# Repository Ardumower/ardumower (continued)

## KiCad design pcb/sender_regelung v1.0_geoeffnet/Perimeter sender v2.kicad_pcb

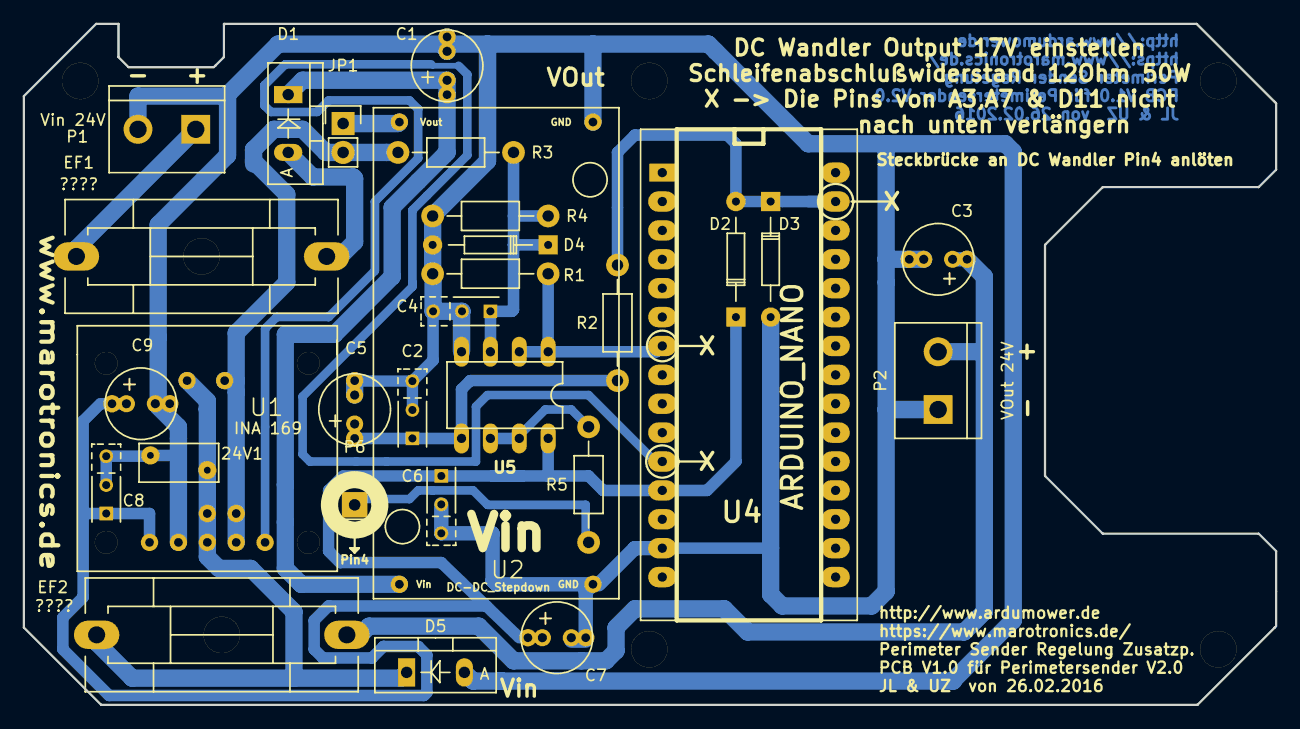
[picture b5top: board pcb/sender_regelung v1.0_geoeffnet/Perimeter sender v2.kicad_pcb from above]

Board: 2 copper layers, 110.1 x 59.9 mm, 35 parts (0 on the bottom side), 16 nets.

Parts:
24V1: VR; RV_Disc_D7_W3.4_P5
B1, B2, B3, B5, B6: Bohrloch_3,2mm
C1, C3: 220uF/63V; Elko_vert_11.2x6.3mm_RM2.5_RM5.0
C2: 220nF; C_Rect_L4_W2.5_P2.5_P5.0
C4: 47pP; C_Rect_L4_W2.5_P2.5_P5.0
C5: 47uF/16V; Elko_vert_11.2x6.3mm_RM2.5_RM5.0
C6, C8: 100nF; C_Rect_L4_W2.5_P2.5_P5.0
C7, C9: 10uF/16V; Elko_vert_11.2x6.3mm_RM2.5_RM5.0
D1, D5: MBR 1045; Diode_TO-220_Vertical
D2, D3: 1N4148; Diode_DO-35_SOD27_Horizontal_RM10
D4: ZPD5,1V; Diode_DO-35_SOD27_Horizontal_RM10
EF1, EF2: ????; Fuseholder_Reichelt_PL112000
JP1: PWR; Pin_Header_Straight_1x02
P1: Vin 24V; Anschlussklemme_2P_RM5,08
P2: VOut 24V; Anschlussklemme_2P_RM5,08
P6: Pin4; Pin_Header_Straight_1x01
R1, R4: 10K/1%; Resistor_Horizontal_RM10mm
R2: 47K; Resistor_Horizontal_RM10mm
R3: 100K/1%; Resistor_Horizontal_RM10mm
R5: 1K; Resistor_Horizontal_RM10mm
U1: INA 169; INA169
U2: DC-DC_Stepdown; DC_DC_DSN2596_mit_Bohrloch
U4: ARDUINO_NANO; arduino_nano
U5: OPA2340PA; 40xx-DIL08

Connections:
+5V: C6.1, C7.1, C8.1, C9.1, D2.1, U1.1, U4.5V, U5.8
A3: R1.1, U4.A3, U5.1, U5.2
A7: U1.3, U4.A7
D11: D2.2, D3.1, R2.2, U4.D11
DC_Wandler_Pin_4: P6.1, R5.1
GND: 24V1.2, C1.2, C2.2, C3.2, C4.2, C5.2, C6.2, C7.2, C8.2, C9.2, D3.2, D4.2, D5.2, P1.2, P2.1, R1.2, R4.2, U1.2, U2.1, U2.4, U4.GND1, U5.4
unnamed: 24V1.1, D5.1, EF2.2, U1.5
unnamed: C1.1, D1.1, U2.3
unnamed: C2.1, C5.1, R2.1, U5.5
unnamed: C3.1, EF2.1, P2.2
unnamed: C4.1, D4.1, R3.2, R4.1, U5.3
unnamed: D1.2, EF1.1
unnamed: EF1.2, P1.1
unnamed: JP1.1, U2.2
unnamed: JP1.2, R3.1, U1.4
unnamed: R5.2, U5.6, U5.7

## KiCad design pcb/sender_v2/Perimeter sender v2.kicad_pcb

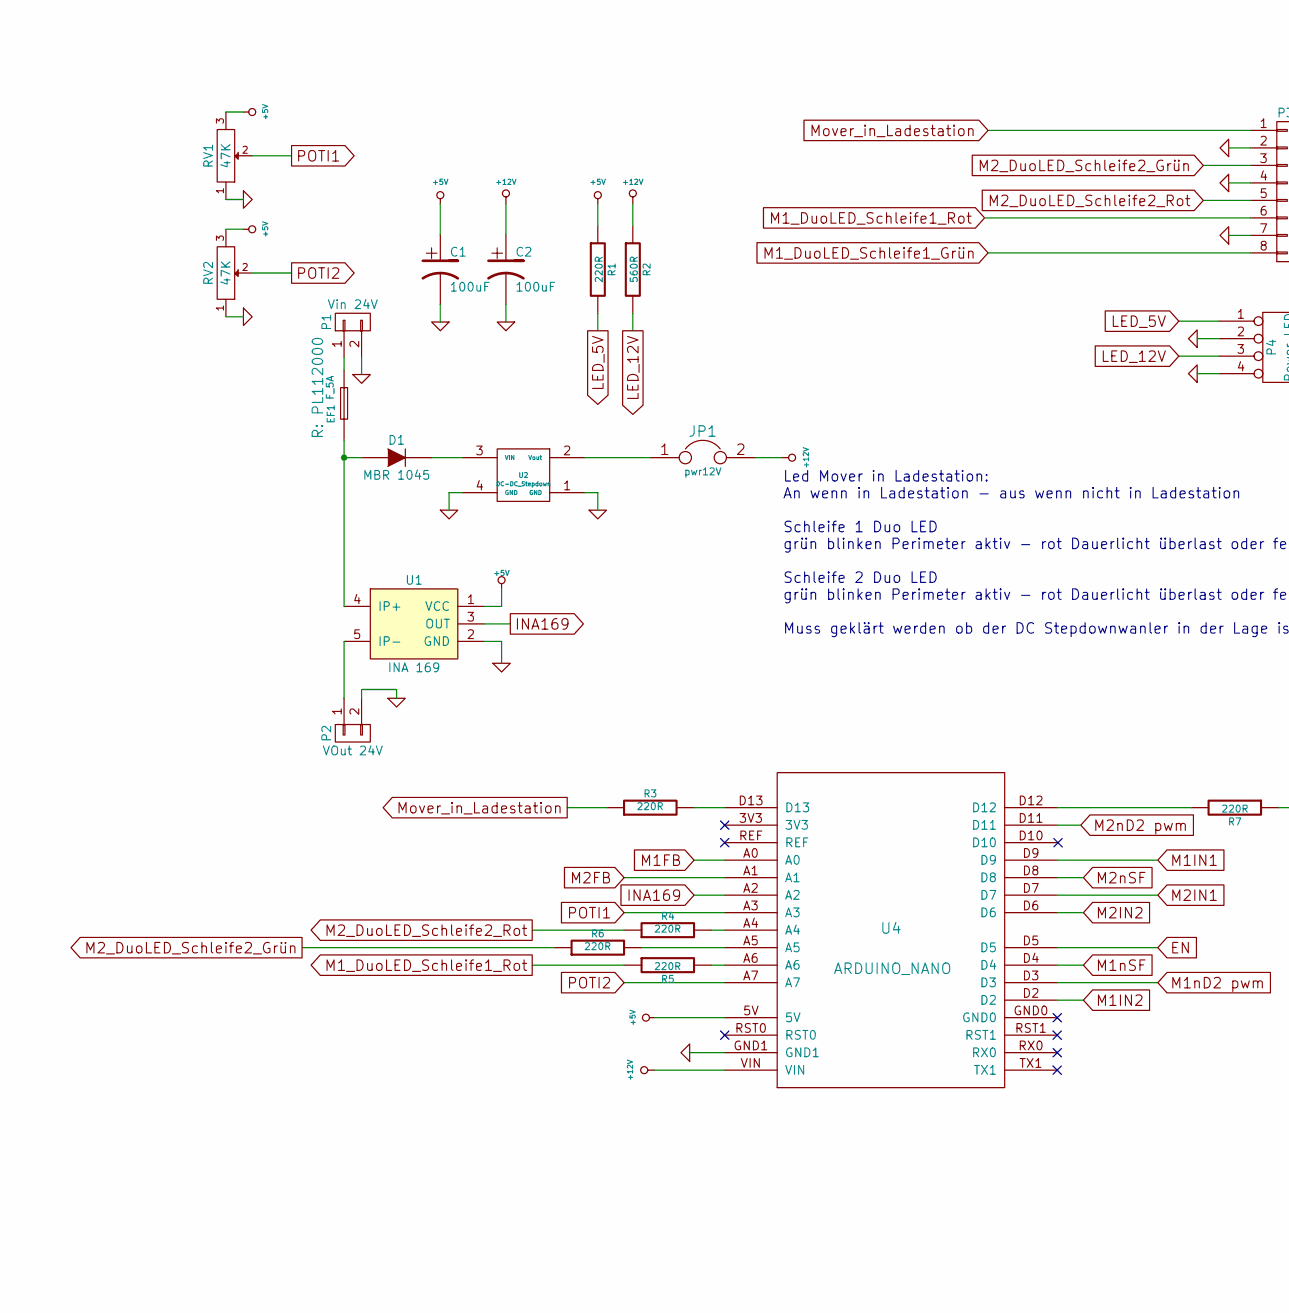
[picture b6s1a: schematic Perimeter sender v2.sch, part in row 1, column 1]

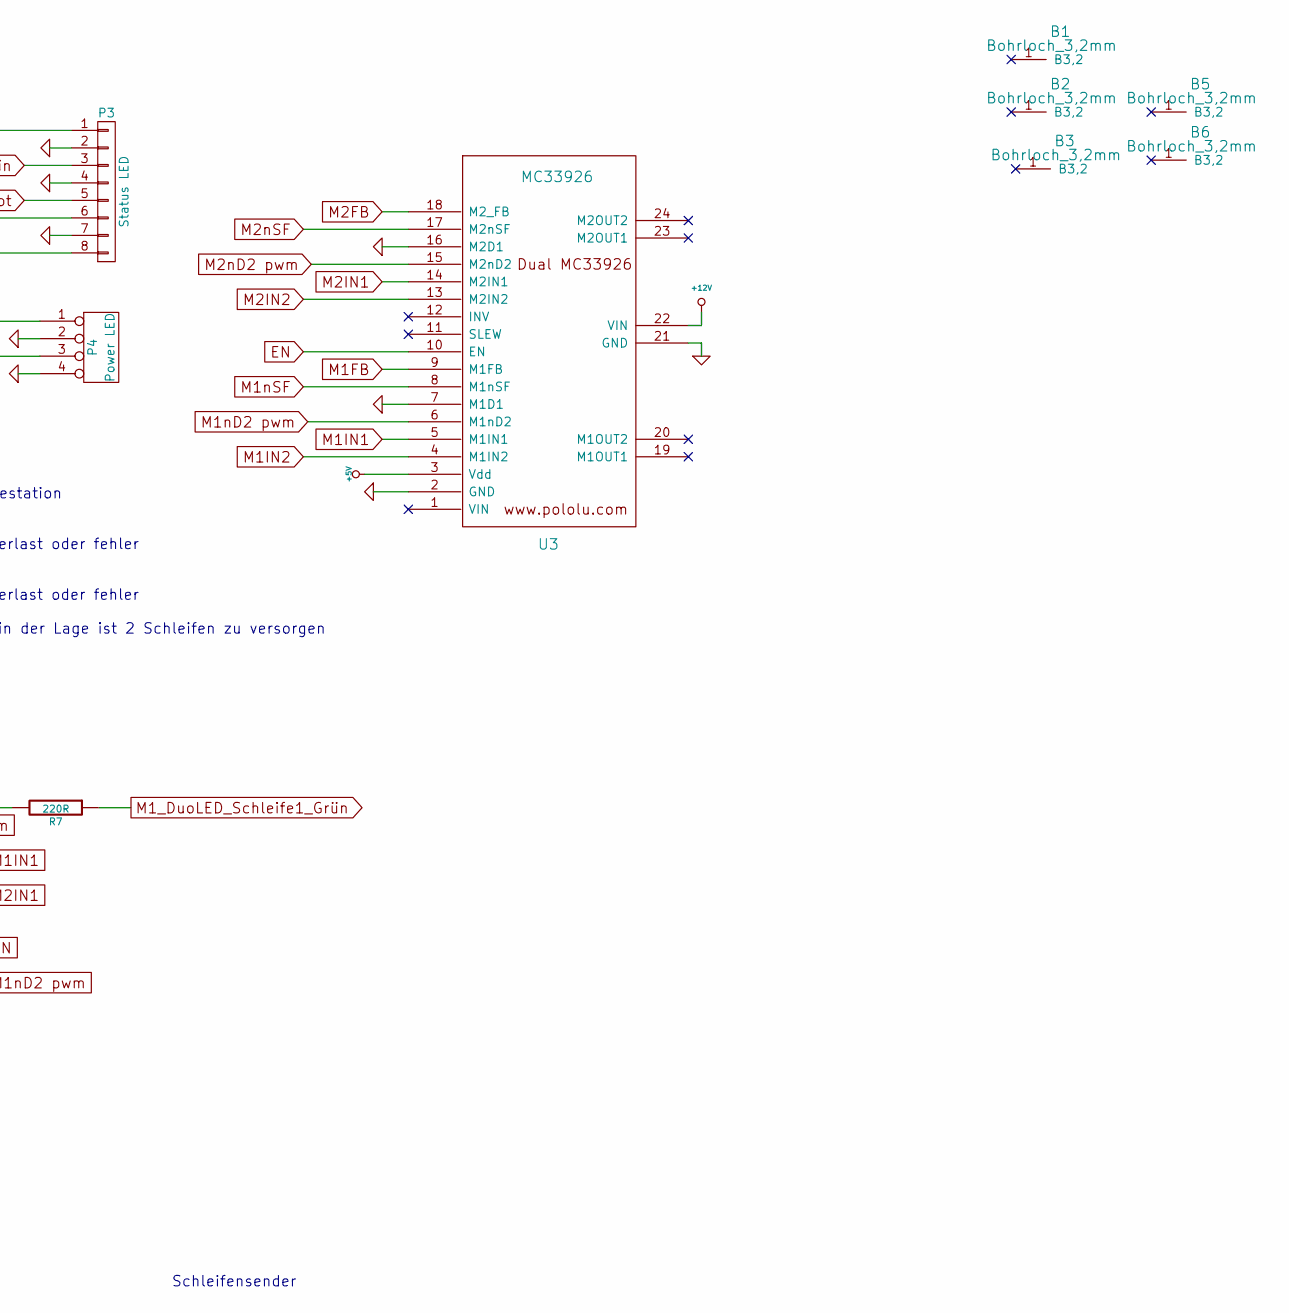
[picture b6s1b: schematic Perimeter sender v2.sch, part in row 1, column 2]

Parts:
B1, B2, B3, B5, B6: Bohrloch_3,2mm
C1, C2: 100uF; Elko_vert_11.2x6.3mm_RM2.5_RM5.0
D1: MBR 1045; MBR1045_Horizontal
EF1: F_5A; Fuseholder_Reichelt_PL112000
JP1: pwr12V; Pin_Header_Straight_1x02
P1: Vin 24V; Anschlussklemme_2P_RM5,08
P2: VOut 24V; Anschlussklemme_2P_RM5,08
P3: Status LED; Pin_Header_Straight_1x08
P4: Power LED; Pin_Header_Straight_1x04
R1, R3, R4, R5, R6, R7: 220R; Resistor_Horizontal_RM10mm
R2: 560R; Resistor_Horizontal_RM10mm
RV1, RV2: 47K; Potentiometer_VishaySpectrol-Econtrim-Type36T_3D-angepasst_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
U1: INA 169; INA169
U2: DC-DC_Stepdown; DC_DC_DSN2596_mit_Bohrloch
U3: MC33926; MC_33926_31polig_mit_Bohrloch_neue_Masse
U4: ARDUINO_NANO; arduino_nano

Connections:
+5V: C1.1, R1.1, RV1.3, RV2.3, U1.1 (VCC), U3.3 (Vdd), U4.5V
+12V: C2.1, JP1.2, R2.1, U3.22 (VIN), U4.VIN
EN: U3.10 (EN), U4.D5
GND: C1.2, C2.2, P1.2, P2.2, P3.2, P3.4, P3.7, P4.2, P4.4, RV1.1, RV2.1, U1.2 (GND), U2.1 (GND), U2.4 (GND), U3.2 (GND), U3.7 (M1D1), U3.16 (M2D1), U3.21 (GND), U4.GND1
INA169: U1.3 (OUT), U4.A2
LED_5V: P4.1, R1.2
LED_12V: P4.3, R2.2
M1FB: U3.9 (M1FB), U4.A0
M1IN1: U3.5 (M1IN1), U4.D9
M1IN2: U3.4 (M1IN2), U4.D2
M1_DuoLED_Schleife1_Grün: P3.8, R7.1
M1_DuoLED_Schleife1_Rot: P3.6, R5.1
M1nD2 pwm: U3.6 (M1nD2), U4.D3
M1nSF: U3.8 (M1nSF), U4.D4
M2FB: U3.18 (M2_FB), U4.A1
M2IN1: U3.14 (M2IN1), U4.D7
M2IN2: U3.13 (M2IN2), U4.D6
M2_DuoLED_Schleife2_Grün: P3.3, R6.1
M2_DuoLED_Schleife2_Rot: P3.5, R4.1
M2nD2 pwm: U3.15 (M2nD2), U4.D11
M2nSF: U3.17 (M2nSF), U4.D8
Mover_in_Ladestation: P3.1, R3.1
unnamed: D1.1 (A), EF1.1, U1.4 (IP+)
unnamed: D1.2 (K), U2.3 (VIN)
unnamed: EF1.2, P1.1
unnamed: JP1.1, U2.2 (Vout)
unnamed: P2.1, U1.5 (IP-)
unnamed: R3.2, U4.D13
unnamed: R4.2, U4.A4
unnamed: R5.2, U4.A6
unnamed: R6.2, U4.A5
unnamed: R7.2, U4.D12
POTI1: RV1.2, U4.A3
POTI2: RV2.2, U4.A7

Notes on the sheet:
Led Mover in Ladestation: An wenn in Ladestation - aus wenn nicht in Ladestation Schleife 1 Duo LED grün blinken Perimeter aktiv - rot Dauerlicht überlast oder fehler Schleife 2 Duo LED grün blinken Perimeter aktiv - rot Dauerlicht überlast oder fehler Muss geklärt werden ob der DC Stepdownwanler i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
Schleifensender

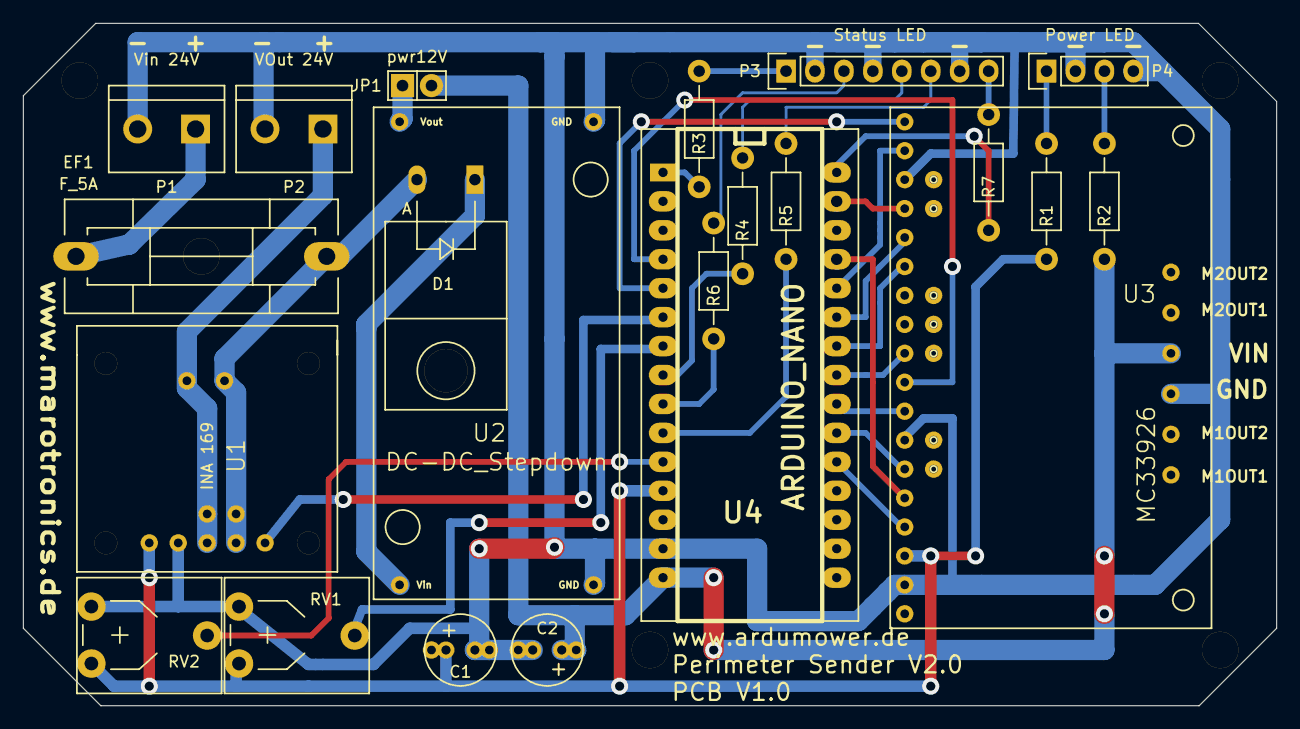
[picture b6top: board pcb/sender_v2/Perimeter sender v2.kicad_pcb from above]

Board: 2 copper layers, 110.0 x 59.9 mm, 27 parts (0 on the bottom side), 34 nets.
